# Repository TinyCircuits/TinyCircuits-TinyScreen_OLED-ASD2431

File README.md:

# TinyCircuits TinyScreen OLED Display
# ASD2431 Rev6

The design files are located under design_files/ for the TinyCircuits TinyScreen PCB Rev6.  This is a TinyShield board that includes a 96x64 Color OLED Display.  

Format is in Cadsoft Eagle format - Eagle version 6.2 was used for the original design.

For more infomation on this, check out the product page at TinyCircuits.com: https://tinycircuits.com/collections/leds-displays/products/tinyscreen

# License:

Design by TinyCircuits.
All design files are released under the Creative Commons Attribution Share-Alike 3.0 License, see the following link for details: http://creativecommons.org/licenses/by-sa/3.0

All text above must be included in any redistribution or derived design

This project uses designs and concepts developed as part of the Arduino project and the LilyPad project.  The TinyCircuits design files themselves (schematics, PCB and libraries) are not directly derived from these works' design files and have been created new, however the concepts and basic architecture behind the TinyDuino and TinyLily products are derived and we thank the hard work of the organizations below for their contributions to open-source hardware:
  
Original Arduino Uno Design by Team Arduino

LilyPad Arduino Design by Leah Buechley and Sparkfun Electronics

Please support the open-source hardware community

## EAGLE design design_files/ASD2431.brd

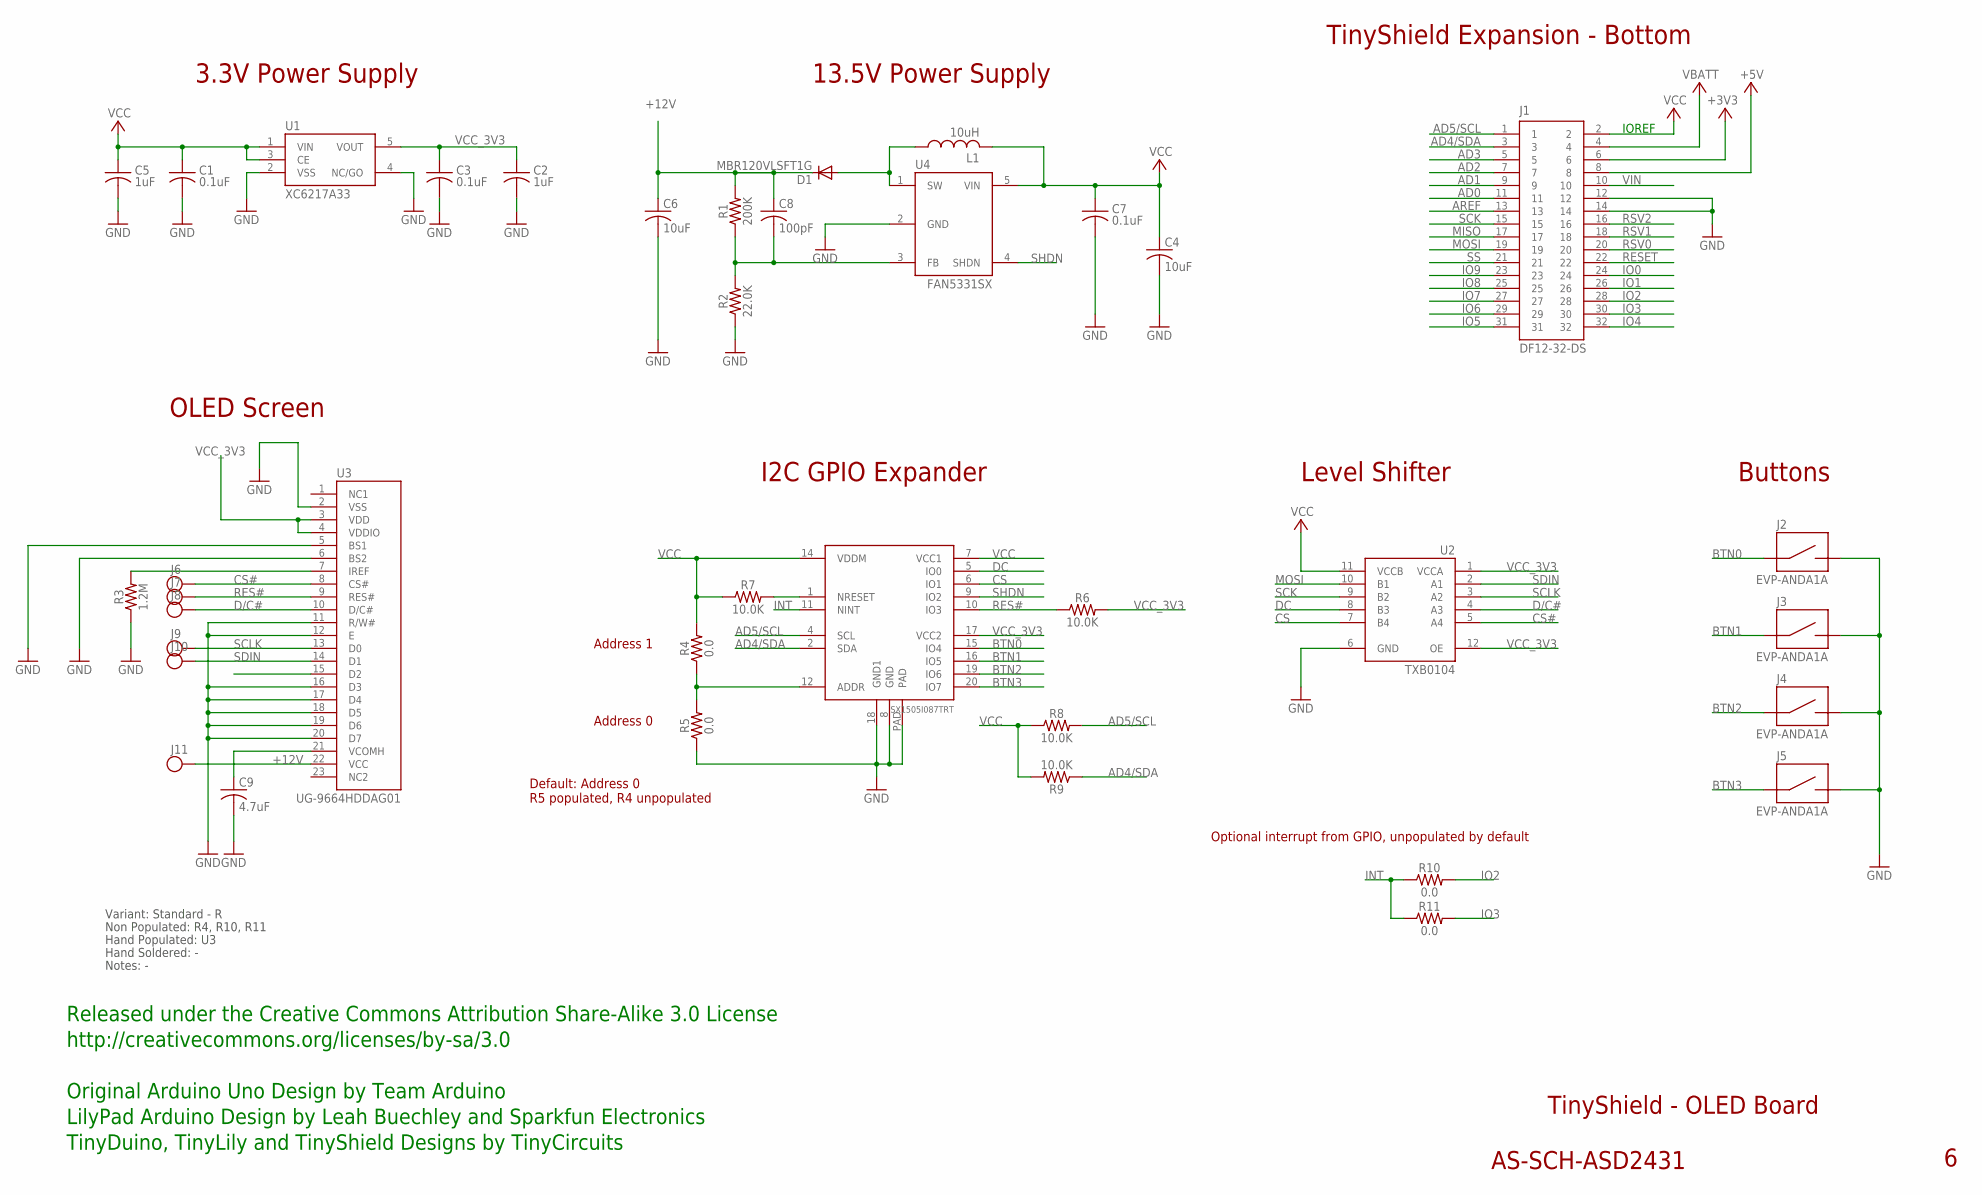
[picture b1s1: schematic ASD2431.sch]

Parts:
C1, C3, C7: 0.1uF; C0402; PARTNO AS-ITM-00008
C2, C5: 1uF; C0402; PARTNO AS-ITM-00105
C4, C6: 10uF; C0805; PARTNO AS-ITM-00045
C8: 100pF; 0402; PARTNO AS-ITM-00148
C9: 4.7uF; 1206_CAP_TANT; PARTNO AS-ITM-00232
D1: MBR120VLSFT1G; SOD-123FL
J1: DF12-32-DS; PARTNO AS-ITM-00012
J2, J3, J4, J5: EVP-ANDA1A; PTS840GKP; PARTNO AS-ITM-00236
J6, J7, J8, J9, J10, J11: TEST_POINT; TEST_POINT_1MM
L1: 10uH; R0805
R1: 200K; 0402; PARTNO AS-ITM-00178
R2: 22.0K; 0402; PARTNO AS-ITM-00147
R3: 1.2M; 0402; PARTNO AS-ITM-00280
R4, R5: 0.0; 0402
R6: 10.0K; 0402
R7, R8, R9: 10.0K; 0402; PARTNO AS-ITM-00032
R10, R11: 0.0; 0402; PARTNO AS-ITM-00076
U1: XC6217A33; SOT-25; PARTNO AS-ITM-00249
U2: TXB0104; UQFN-12
U3: UG-9664HDDAG01; OLED_DISPLAY
U4: FAN5331SX; SOT-23
U5: SX1505I087TRT; QFN-UT20

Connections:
+3V3: J1.6
+5V: J1.8
+12V: C6.1, C8.1, D1.C, J11.P$1, R1.2, U3.22 (VCC)
AD0: J1.11
AD1: J1.9
AD2: J1.7
AD3: J1.5
AD4/SDA: J1.3, R9.1, U5.2 (SDA)
AD5/SCL: J1.1, R8.2, U5.4 (SCL)
AREF: J1.13
BTN0: J2.1, J2.2 (1), U5.15 (IO4)
BTN1: J3.1, J3.2 (1), U5.16 (IO5)
BTN2: J4.1, J4.2 (1), U5.19 (IO6)
BTN3: J5.1, J5.2 (1), U5.20 (IO7)
CS: U2.7 (B4), U5.6 (IO1)
CS#: J6.P$1, U2.5 (A4), U3.8 (CS#)
D/C#: J8.P$1, U2.4 (A3), U3.10 (D/C#)
DC: U2.8 (B3), U5.5 (IO0)
GND: C1.2, C2.2, C3.2, C4.2, C5.2, C6.2, C7.2, C9.2, J1.12, J1.14, J2.3 (2), J2.4 (2), J3.3 (2), J3.4 (2), J4.3 (2), J4.4 (2), J5.3 (2), J5.4 (2), R2.1, R3.1, R5.1, U1.2 (VSS), U1.4 (NC/GO), U2.6 (GND), U3.2 (VSS), U3.5 (BS1), U3.6 (BS2), U3.11 (R/W#), U3.12 (E), U3.16 (D3), U3.17 (D4), U3.18 (D5), U3.19 (D6), U3.20 (D7), U4.2 (GND), U5.8 (GND), U5.18 (GND1), U5.PAD
INT: R10.1, R11.1, U5.11 (NINT)
IO0: J1.24
IO1: J1.26
IO2: J1.28, R10.2
IO3: J1.30, R11.2
IO4: J1.32
IO5: J1.31
IO6: J1.29
IO7: J1.27
IO8: J1.25
IO9: J1.23
MISO: J1.17
MOSI: J1.19, U2.10 (B1)
unnamed: R7.2, U5.1 (NRESET)
unnamed: D1.A, L1.1, U4.1 (SW)
unnamed: C8.2, R1.1, R2.2, U4.3 (FB)
unnamed: R3.2, U3.7 (IREF)
unnamed: C9.1, U3.21 (VCOMH)
unnamed: R4.1, R5.2, U5.12 (ADDR)
RES#: J7.P$1, R6.1, U3.9 (RES#), U5.10 (IO3)
RESET: J1.22
RSV0: J1.20
RSV1: J1.18
RSV2: J1.16
SCK: J1.15, U2.9 (B2)
SCLK: J9.P$1, U2.3 (A2), U3.13 (D0)
SDIN: J10.P$1, U2.2 (A1), U3.14 (D1)
SHDN: U4.4 (SHDN), U5.9 (IO2)
SS: J1.21
VBATT: J1.4
VCC: C1.1, C4.1, C5.1, C7.1, J1.2, L1.2, R4.2, R7.1, R8.1, R9.2, U1.1 (VIN), U1.3 (CE), U2.11 (VCCB), U4.5 (VIN), U5.7 (VCC1), U5.14 (VDDM)
VCC_3V3: C2.1, C3.1, R6.2, U1.5 (VOUT), U2.1 (VCCA), U2.12 (OE), U3.3 (VDD), U3.4 (VDDIO), U5.17 (VCC2)
VIN: J1.10

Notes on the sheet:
TinyShield Expansion - Bottom
TinyShield - OLED Board
AS-SCH-ASD2431
IOREF
Released under the Creative Commons Attribution Share-Alike 3.0 License
http://creativecommons.org/licenses/by-sa/3.0
LilyPad Arduino Design by Leah Buechley and Sparkfun Electronics
TinyDuino, TinyLily and TinyShield Designs by TinyCircuits
Original Arduino Uno Design by Team Arduino
3.3V Power Supply
13.5V Power Supply
OLED Screen
Level Shifter
I2C GPIO Expander
Buttons
Address 0
Address 1
Default: Address 0 R5 populated, R4 unpopulated
Optional interrupt from GPIO, unpopulated by default
Non Populated: R4, R10, R11
Hand Populated: U3
Hand Soldered: -
Notes: -
Variant: Standard - R

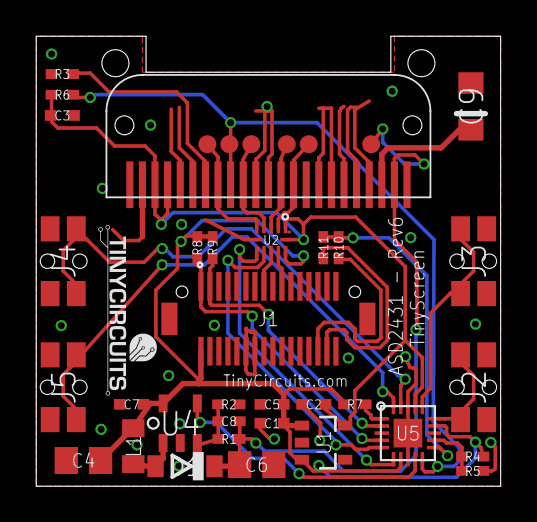
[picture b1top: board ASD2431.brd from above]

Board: 2 copper layers, 25.8 x 25.0 mm, 39 parts (0 on the bottom side), 29 nets.

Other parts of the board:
U$1: DOCFIELD-TINYCIRCUITS-PCB

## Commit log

2015-04-11 :lollipop: Added .gitattributes & .gitignore files
2015-06-07 Update to rev 5
2019-01-02 update files
2019-05-20 added example code
2019-05-20 updated naming and formatting
2019-05-22 added images
2020-02-11 image update
2020-07-28 Add CAD data
2020-08-14 Update CAD drawing
